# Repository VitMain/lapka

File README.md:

# Лапка

Беспроводная эргономичная сплит-клавиатура для тех, у кого лапки (:

**Особенности:**
- 36 клавиш, совместима с Choc v2 свитчами
- Direct-pin подключение — при сборке не требуются диоды
- Низкопрофильный корпус (свитчи практически касаются стола)

**Структура репозитория:**

| Директория | Описание                                              |
| ---------: | :---------------------------------------------------- |
|        3MF | Проект OrcaSlicer (для примера параметров печати)     |
|     Assets | Изображения и фото                                    |
|     Fusion | Проект Autodesk Fusion 360                            |
|    Gerbers | Gerber-файлы для производства плат                    |
|      Guide | Описание [процесса сборки](./Guide/build-guide-ru.md) |
|      KiCad | Проект KiCad (схема, плата, компоненты)               |
|        STL | 3D-модели частей корпуса                              |

Ссылки на актуальные прошивки:
- [ZMK](https://github.com/braindefender/lapka-zmk-config)
- [RMK](https://github.com/braindefender/lapka-rmk-config)

## RMK

Следуйте инструкциям в README.md репозитория с RMK прошивкой.

## ZMK

Используйте вариант подключения direct-pin, описанный в `lapka_wellum36_left.overlay` и `lapka_wellum36_right.overlay`.

Откройте GitHub Actions и найдите последний успешно собранный билд ветки `lapka-36`.
В нём будет артефакт сборки `firmware.zip`, который содержит все нужные для прошивки файлы.

Тестовая прошивка расположена в ветке `lapka-36-test`. В ней всего один слой и клавиши на тамб-кластере заменены на F1-F6. Это позволит увидеть нажатия клавиш на [key-test.ru](https://key-test.ru).

## История изменений

### v2.2
- Добавлена ссылка на репозиторий прошивки RMK

### v2.1
- Изменена ссылка на репозиторий прошивки ZMK

### v2
- Добавлена поддержка Choc v1
- Изменена разметка пинов
- Обновлена шелкография, логотип перенесён на Cu слой
- Добавлен проект Fusion 360

### v1
- Первый релиз. Только для Choc v2

# Lapka

Wireless ergonomic split keyboard for those who have paws (:

**Peculiarities:**
- 36 keys, Choc v2 compatible
- Direct-pin connection — no diodes needed required
- Low-profile case (switches almost touch the table)

**Repository structure:**

| Directory | Description                                            |
| --------: | :----------------------------------------------------- |
|       3MF | OrcaSlicer project files (printing parameters example) |
|    Assets | Images and photos                                      |
|    Fusion | Autodesk Fusion 360 project                            |
|   Gerbers | Gerber-files for PCB production                        |
|     Guide | [Build guide](./Guide/build-guide-en.md)               |
|     KiCad | KiCad project (schematics, PCB design, components)     |
|       STL | 3D-models of case parts                                |

Links to the current firmwares:
- [ZMK](https://github.com/braindefender/lapka-zmk-config).
- [RMK](https://github.com/braindefender/lapka-rmk-config).

## RMK

Follow the instructions in the README.md file of the RMK firmware repository.

## ZMK

Use direct pin layout, described in `lapka_wellum36_left.overlay` and `lapka_wellum36_right.overlay`.

Open GitHub Actions and find latest successful build of branch `lapka-36`.
In that build you'll find artifact `firmware.zip`, which contain all the neccessary firmware files.

Test firmware is located in branch `lapka-36-test`. There are single layer with F1-F6 keys on the thumb-cluster. That will help to see keypresses on the [key-test.ru](https://key-test.ru).

## Changelog

### v2.2
- Added link to RMK Firmware repo

### v2.1
- Changed link to ZMK Firmware repo

### v2
- Added support for Choc v1
- Changed pin layout
- Updated silk-screen, moved logo to Cu layer
- Added Fusion 360 project

### v1
- Initial release. Only for Choc v2

## Фото / Photos

### Original

### From awesome people

> by [Макс / f1dell](https://t.me/f1dell)

> by [Иосиф Правец](https://t.me/pravets_IT)

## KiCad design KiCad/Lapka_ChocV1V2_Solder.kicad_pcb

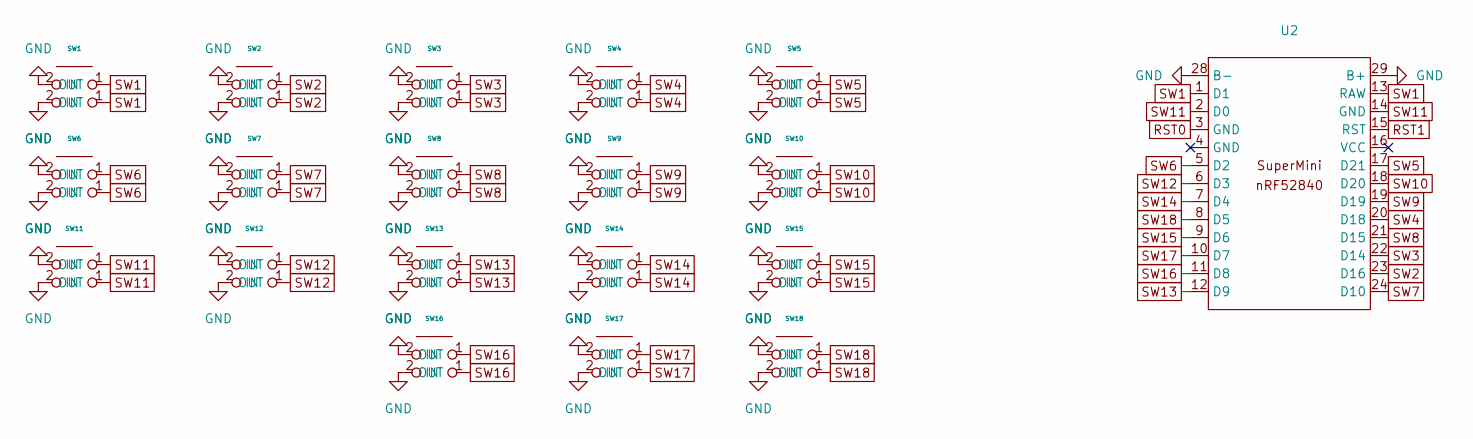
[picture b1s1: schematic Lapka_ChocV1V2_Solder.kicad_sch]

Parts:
SW1, SW2, SW3, SW4, SW5, SW6, SW7, SW8, SW9, SW10, SW11, SW12, SW13, SW14, SW15, SW16, SW17, SW18: SW_KLPv1v2_DS
U2: SuperMini NRF52840

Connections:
GND: SW1.2 (IN), SW2.2 (IN), SW3.2 (IN), SW4.2 (IN), SW5.2 (IN), SW6.2 (IN), SW7.2 (IN), SW8.2 (IN), SW9.2 (IN), SW10.2 (IN), SW11.2 (IN), SW12.2 (IN), SW13.2 (IN), SW14.2 (IN), SW15.2 (IN), SW16.2 (IN), SW17.2 (IN), SW18.2 (IN), U2.28 (B-), U2.29 (B+)
RST0: U2.3 (GND)
RST1: U2.15 (RST)
SW1: SW1.1 (OUT), U2.1 (D1), U2.13 (RAW)
SW2: SW2.1 (OUT), U2.23 (D16)
SW3: SW3.1 (OUT), U2.22 (D14)
SW4: SW4.1 (OUT), U2.20 (D18)
SW5: SW5.1 (OUT), U2.17 (D21)
SW6: SW6.1 (OUT), U2.5 (D2)
SW7: SW7.1 (OUT), U2.24 (D10)
SW8: SW8.1 (OUT), U2.21 (D15)
SW9: SW9.1 (OUT), U2.19 (D19)
SW10: SW10.1 (OUT), U2.18 (D20)
SW11: SW11.1 (OUT), U2.2 (D0), U2.14 (GND)
SW12: SW12.1 (OUT), U2.6 (D3)
SW13: SW13.1 (OUT), U2.12 (D9)
SW14: SW14.1 (OUT), U2.7 (D4)
SW15: SW15.1 (OUT), U2.9 (D6)
SW16: SW16.1 (OUT), U2.11 (D8)
SW17: SW17.1 (OUT), U2.10 (D7)
SW18: SW18.1 (OUT), U2.8 (D5)

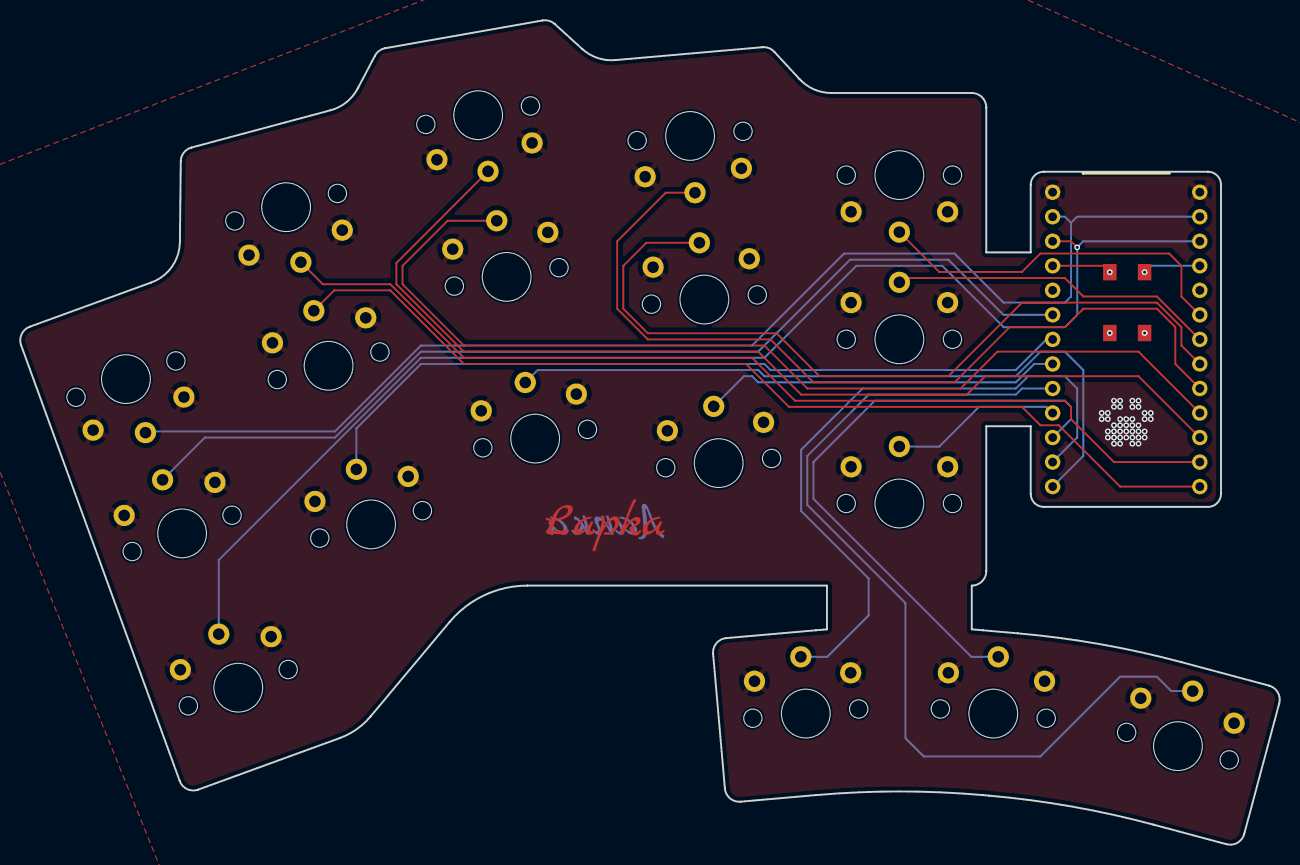
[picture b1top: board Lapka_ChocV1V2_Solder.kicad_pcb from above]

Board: 2 copper layers, 130.4 x 85.4 mm, 19 parts (0 on the bottom side), 19 nets.

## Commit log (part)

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2025-04-15 feat: initial release
2025-04-15 feat: add repo structure
2025-04-15 feat: add build guide
2025-04-15 feat: update readme
2025-04-15 feat: add direct pin notice
2025-04-15 feat: add license
2025-04-15 feat: add photos
2025-05-01 major: add choc-v1 support
2025-05-01 fix: readme assets link
2025-05-01 fix: move logos to Cu layers
2025-05-01 fix: update changelog
2025-06-15 feat: update build guide
2025-11-19 feat: update zmk-firmware link
2025-11-29 feat: update images
2026-02-06 fix: zmk firmware link
